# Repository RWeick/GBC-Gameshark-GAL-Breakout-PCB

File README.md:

# GBC-Gameshark-GAL-Breakout-PCB
My custom PCB enabling logic analysis of all relevant pins on the GAL.

This PCB is designed for use with the following GBA slot: https://www.aliexpress.com/item/4000290191316.html

The pin headers are 2.54 mm. I have also included a 3D printable insert for this PCB to the Gameboy Advance / GBA SP.

PCB Thickness: 0.8 mm

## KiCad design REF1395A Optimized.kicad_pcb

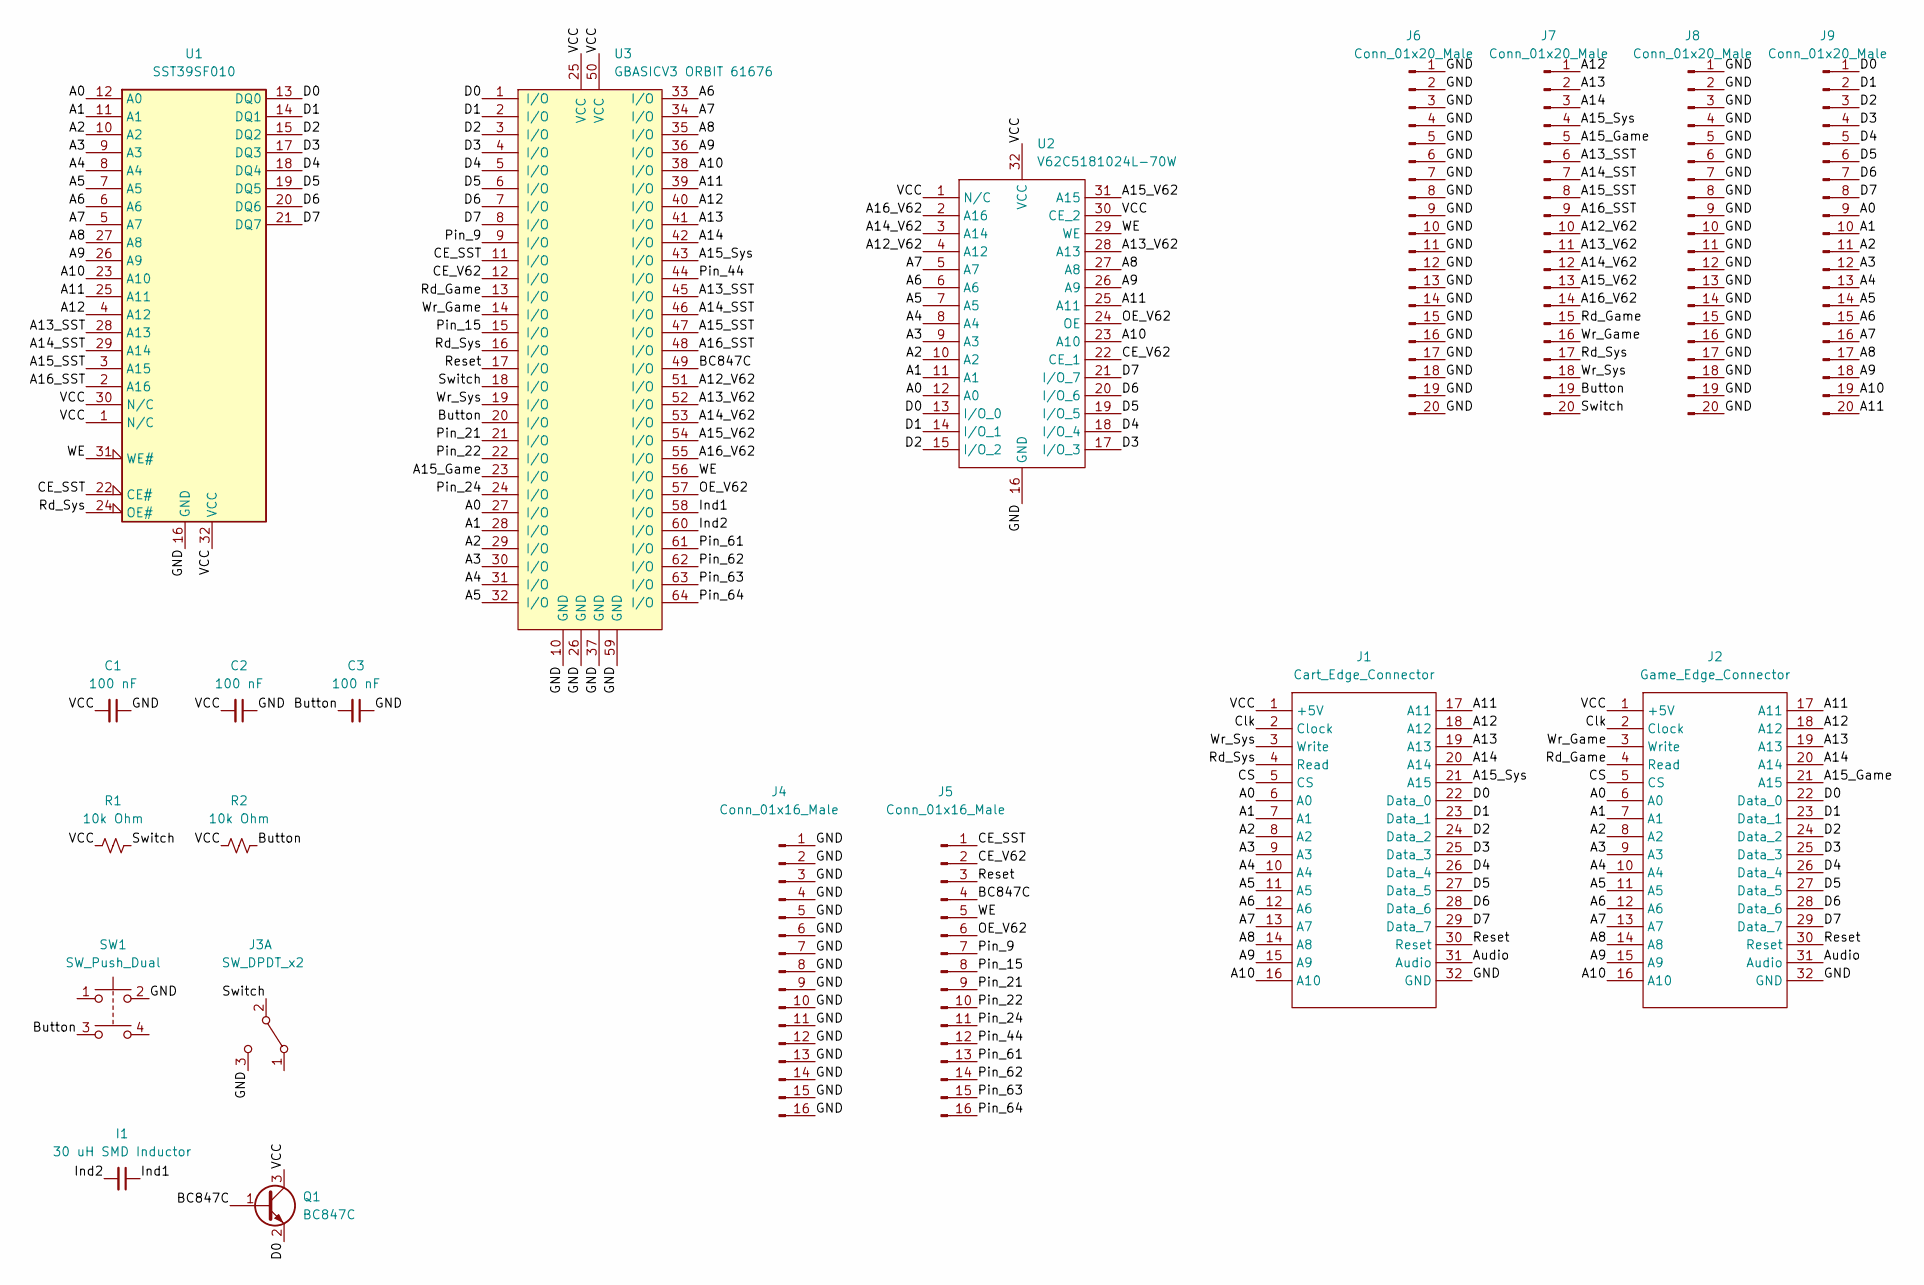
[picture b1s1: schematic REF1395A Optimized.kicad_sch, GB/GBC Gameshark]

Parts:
C1, C2, C3: 100 nF; 100nf Capacitor
I1: 30 uH SMD Inductor; 100nf Capacitor
J1: Cart_Edge_Connector; ACTUAL GAMEBOY EDGE CONNECTOR
J2: Game_Edge_Connector; DSL_Cartridge_Reader
J3: SW_DPDT_x2; Switch_Wide
J4, J5: Conn_01x16_Male; PinHeader_1x16_P2.54mm_Vertical
J6, J7, J8, J9: Conn_01x20_Male; PinHeader_1x20_P2.54mm_Vertical
Q1: BC847C; SOT-23
R1, R2: 10k Ohm; 100nf Capacitor
SW1: SW_Push_Dual; 1mm Side Push Button
U1: SST39SF010; SST 28SF040
U2: V62C5181024L-70W
U3: GBASICV3 ORBIT 61676; LZ9FC17 GAL

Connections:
/A0: J1.6 (A0), J2.6 (A0), J9.9, U1.12 (A0), U2.12 (A0), U3.27 (I/O)
/A1: J1.7 (A1), J2.7 (A1), J9.10, U1.11 (A1), U2.11 (A1), U3.28 (I/O)
/A2: J1.8 (A2), J2.8 (A2), J9.11, U1.10 (A2), U2.10 (A2), U3.29 (I/O)
/A3: J1.9 (A3), J2.9 (A3), J9.12, U1.9 (A3), U2.9 (A3), U3.30 (I/O)
/A4: J1.10 (A4), J2.10 (A4), J9.13, U1.8 (A4), U2.8 (A4), U3.31 (I/O)
/A5: J1.11 (A5), J2.11 (A5), J9.14, U1.7 (A5), U2.7 (A5), U3.32 (I/O)
/A6: J1.12 (A6), J2.12 (A6), J9.15, U1.6 (A6), U2.6 (A6), U3.33 (I/O)
/A7: J1.13 (A7), J2.13 (A7), J9.16, U1.5 (A7), U2.5 (A7), U3.34 (I/O)
/A8: J1.14 (A8), J2.14 (A8), J9.17, U1.27 (A8), U2.27 (A8), U3.35 (I/O)
/A9: J1.15 (A9), J2.15 (A9), J9.18, U1.26 (A9), U2.26 (A9), U3.36 (I/O)
/A10: J1.16 (A10), J2.16 (A10), J9.19, U1.23 (A10), U2.23 (A10), U3.38 (I/O)
/A11: J1.17 (A11), J2.17 (A11), J9.20, U1.25 (A11), U2.25 (A11), U3.39 (I/O)
/A12: J1.18 (A12), J2.18 (A12), J7.1, U1.4 (A12), U3.40 (I/O)
/A12_V62: J7.10, U2.4 (A12), U3.51 (I/O)
/A13: J1.19 (A13), J2.19 (A13), J7.2, U3.41 (I/O)
/A13_SST: J7.6, U1.28 (A13), U3.45 (I/O)
/A13_V62: J7.11, U2.28 (A13), U3.52 (I/O)
/A14: J1.20 (A14), J2.20 (A14), J7.3, U3.42 (I/O)
/A14_SST: J7.7, U1.29 (A14), U3.46 (I/O)
/A14_V62: J7.12, U2.3 (A14), U3.53 (I/O)
/A15_Game: J2.21 (A15), J7.5, U3.23 (I/O)
/A15_SST: J7.8, U1.3 (A15), U3.47 (I/O)
/A15_Sys: J1.21 (A15), J7.4, U3.43 (I/O)
/A15_V62: J7.13, U2.31 (A15), U3.54 (I/O)
/A16_SST: J7.9, U1.2 (A16), U3.48 (I/O)
/A16_V62: J7.14, U2.2 (A16), U3.55 (I/O)
/Audio: J1.31 (Audio), J2.31 (Audio)
/BC847C: J5.4, Q1.1 (B), U3.49 (I/O)
/Button: C3.2, J7.19, R2.1, SW1.3, U3.20 (I/O)
/CE_SST: J5.1, U1.22 (CE#), U3.11 (I/O)
/CE_V62: J5.2, U2.22 (CE_1), U3.12 (I/O)
/CS: J1.5 (CS), J2.5 (CS)
/Clk: J1.2 (Clock), J2.2 (Clock)
/D0: J1.22 (Data_0), J2.22 (Data_0), J9.1, Q1.2 (E), U1.13 (DQ0), U2.13 (I/O_0), U3.1 (I/O)
/D1: J1.23 (Data_1), J2.23 (Data_1), J9.2, U1.14 (DQ1), U2.14 (I/O_1), U3.2 (I/O)
/D2: J1.24 (Data_2), J2.24 (Data_2), J9.3, U1.15 (DQ2), U2.15 (I/O_2), U3.3 (I/O)
/D3: J1.25 (Data_3), J2.25 (Data_3), J9.4, U1.17 (DQ3), U2.17 (I/O_3), U3.4 (I/O)
/D4: J1.26 (Data_4), J2.26 (Data_4), J9.5, U1.18 (DQ4), U2.18 (I/O_4), U3.5 (I/O)
/D5: J1.27 (Data_5), J2.27 (Data_5), J9.6, U1.19 (DQ5), U2.19 (I/O_5), U3.6 (I/O)
/D6: J1.28 (Data_6), J2.28 (Data_6), J9.7, U1.20 (DQ6), U2.20 (I/O_6), U3.7 (I/O)
/D7: J1.29 (Data_7), J2.29 (Data_7), J9.8, U1.21 (DQ7), U2.21 (I/O_7), U3.8 (I/O)
/GND: C1.1, C2.1, C3.1, J1.32 (GND), J2.32 (GND), J3.3 (C), J4.1, J4.2, J4.3, J4.4, J4.5, J4.6, J4.7, J4.8, J4.9, J4.10, J4.11, J4.12, J4.13, J4.14, J4.15, J4.16, J6.1, J6.2, J6.3, J6.4, J6.5, J6.6, J6.7, J6.8, J6.9, J6.10, J6.11, J6.12, J6.13, J6.14, J6.15, J6.16, J6.17, J6.18, J6.19, J6.20, J8.1, J8.2, J8.3, J8.4, J8.5, J8.6, J8.7, J8.8, J8.9, J8.10, J8.11, J8.12, J8.13, J8.14, J8.15, J8.16, J8.17, J8.18, J8.19, J8.20, SW1.2, U1.16 (GND), U2.16 (GND), U3.10 (GND), U3.26 (GND), U3.37 (GND), U3.59 (GND)
/Ind1: I1.1, U3.58 (I/O)
/Ind2: I1.2, U3.60 (I/O)
/OE_V62: J5.6, U2.24 (OE), U3.57 (I/O)
/Pin_9: J5.7, U3.9 (I/O)
/Pin_15: J5.8, U3.15 (I/O)
/Pin_21: J5.9, U3.21 (I/O)
/Pin_22: J5.10, U3.22 (I/O)
/Pin_24: J5.11, U3.24 (I/O)
/Pin_44: J5.12, U3.44 (I/O)
/Pin_61: J5.13, U3.61 (I/O)
/Pin_62: J5.14, U3.62 (I/O)
/Pin_63: J5.15, U3.63 (I/O)
/Pin_64: J5.16, U3.64 (I/O)
/Rd_Game: J2.4 (Read), J7.15, U3.13 (I/O)
/Rd_Sys: J1.4 (Read), J7.17, U1.24 (OE#), U3.16 (I/O)
/Reset: J1.30 (Reset), J2.30 (Reset), J5.3, U3.17 (I/O)
/Switch: J3.2 (B), J7.20, R1.1, U3.18 (I/O)
/VCC: C1.2, C2.2, J1.1 (+5V), J2.1 (+5V), Q1.3 (C), R1.2, R2.2, U1.1 (N/C), U1.30 (N/C), U1.32 (VCC), U2.1 (N/C), U2.30 (CE_2), U2.32 (VCC), U3.25 (VCC), U3.50 (VCC)
/WE: J5.5, U1.31 (WE#), U2.29 (WE), U3.56 (I/O)
/Wr_Game: J2.3 (Write), J7.16, U3.14 (I/O)
/Wr_Sys: J1.3 (Write), J7.18, U3.19 (I/O)

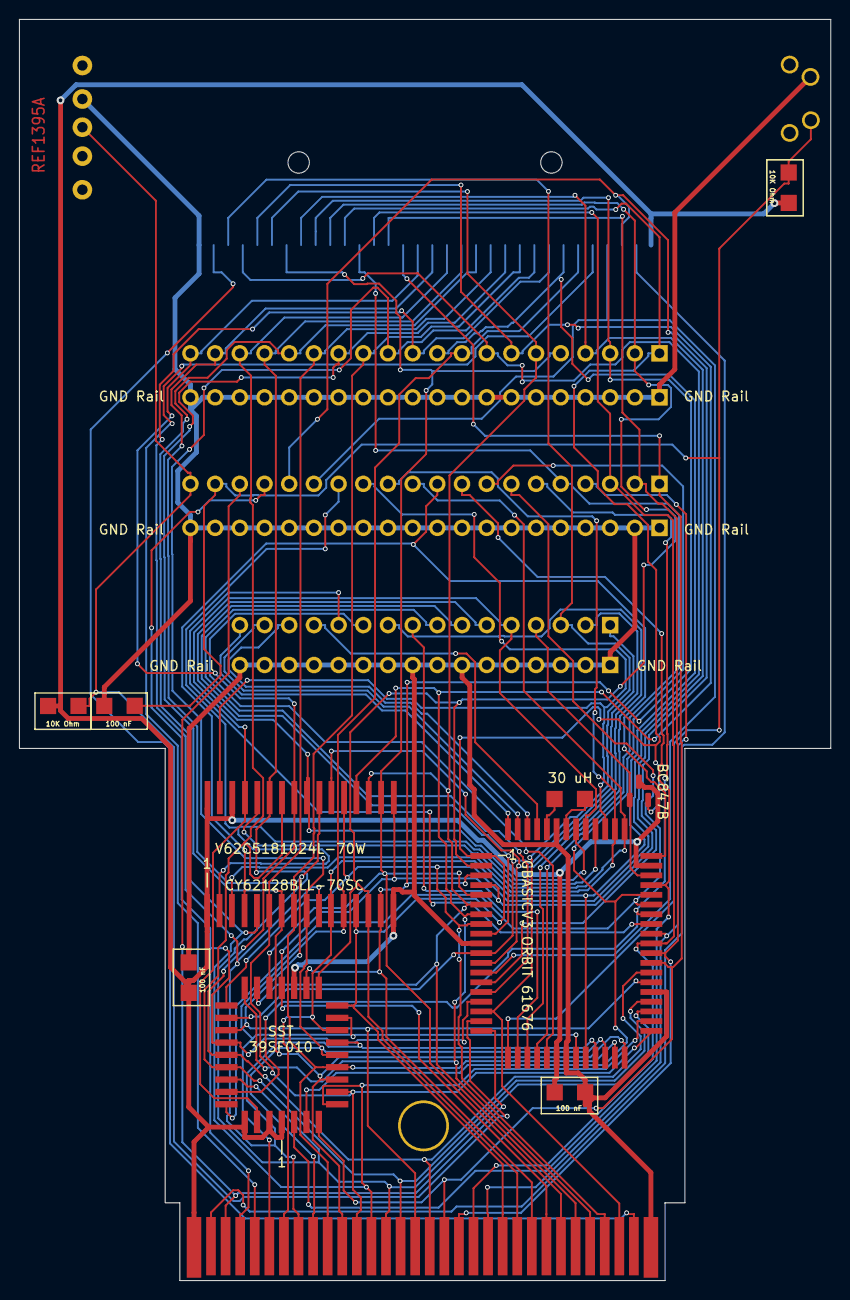
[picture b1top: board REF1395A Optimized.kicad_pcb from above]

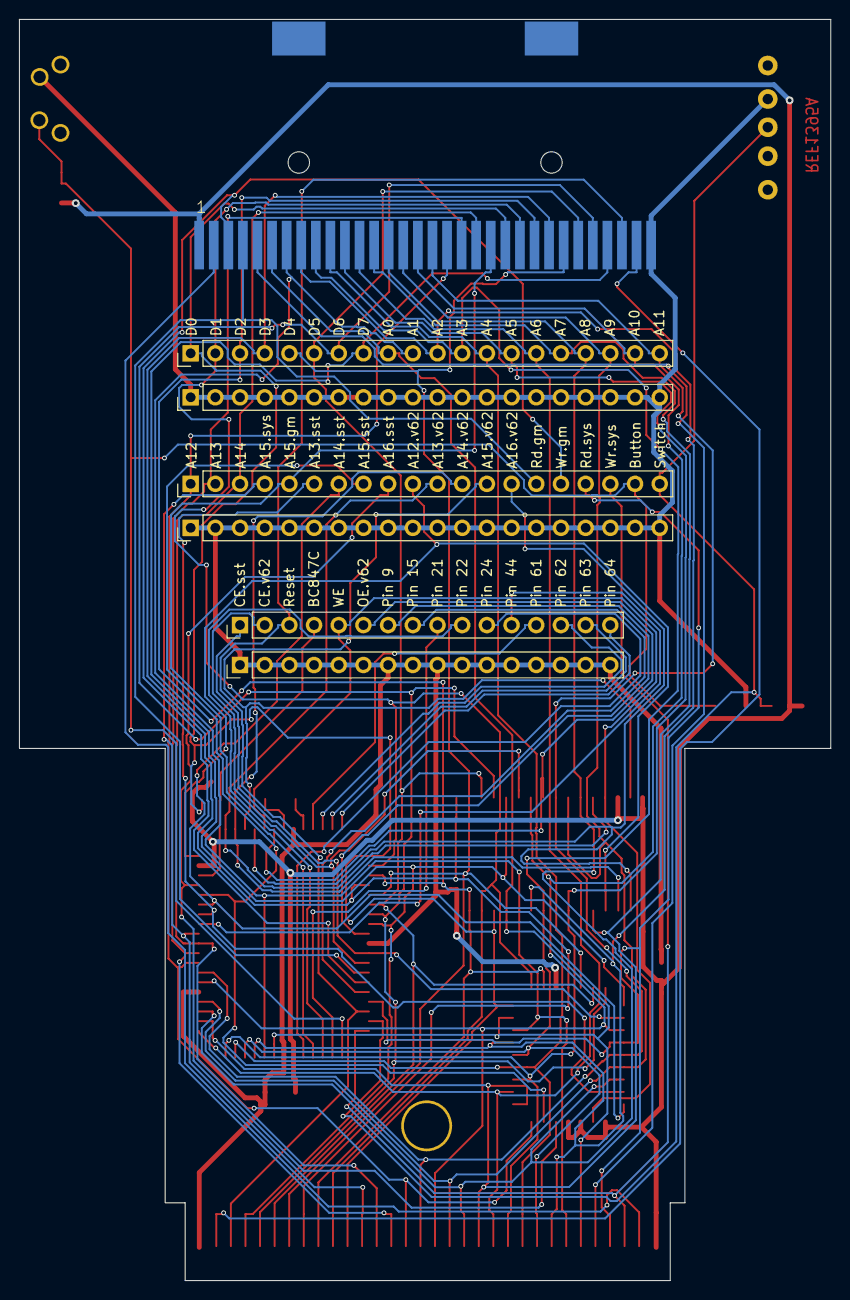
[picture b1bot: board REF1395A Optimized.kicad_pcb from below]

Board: 2 copper layers, 83.5 x 129.8 mm, 21 parts (7 on the bottom side), 63 nets.

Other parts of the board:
Hole: Hole
